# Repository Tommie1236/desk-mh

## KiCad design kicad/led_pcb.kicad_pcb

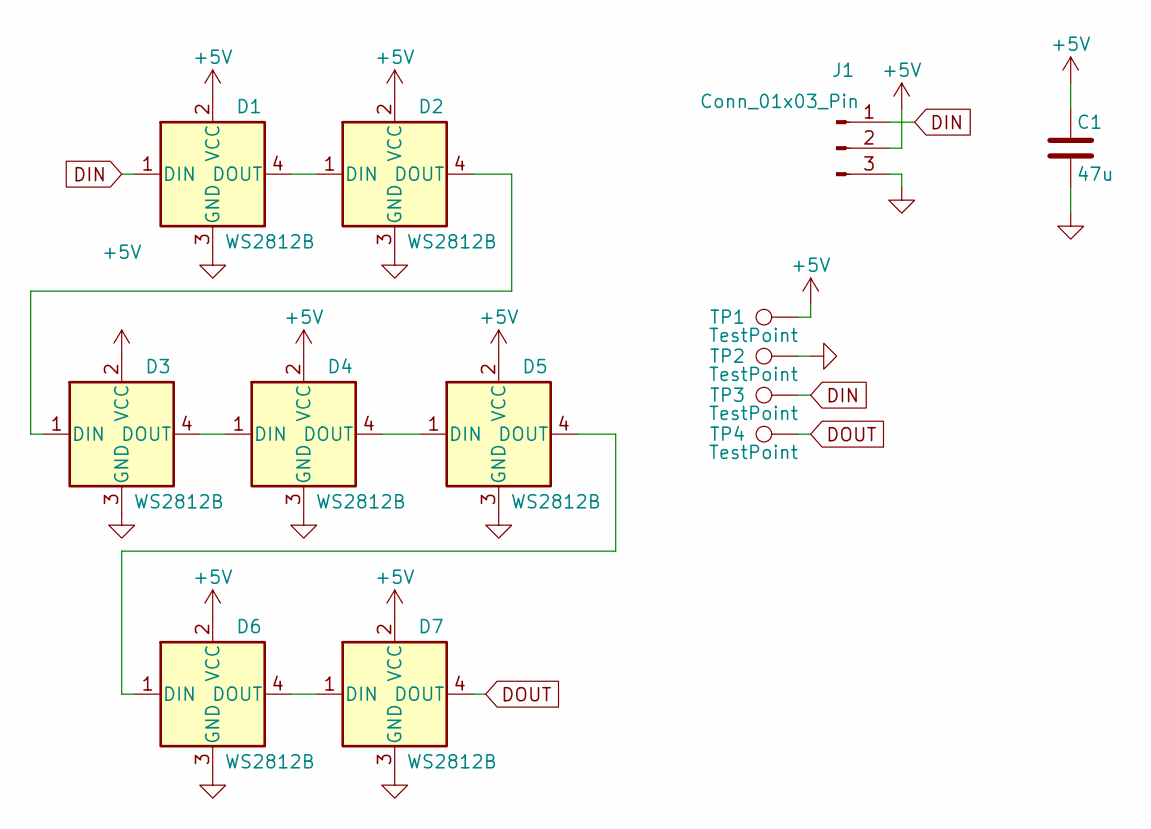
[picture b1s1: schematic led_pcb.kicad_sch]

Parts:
C1: 47u; C_1206_3216Metric
D1, D2, D3, D4, D5, D6, D7: WS2812B; 8mm 4pin
J1: Conn_01x03_Pin; PinHeader_1x03_P1.27mm_Vertical
TP1, TP2, TP3, TP4: TestPoint; TestPoint_Pad_D1.0mm

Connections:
+5V: C1.1, D1.2 (VCC), D2.2 (VCC), D3.2 (VCC), D4.2 (VCC), D5.2 (VCC), D6.2 (VCC), D7.2 (VCC), J1.2, TP1.1
DIN: D1.1 (DIN), J1.1, TP3.1
DOUT: D7.4 (DOUT), TP4.1
GND: C1.2, D1.3 (GND), D2.3 (GND), D3.3 (GND), D4.3 (GND), D5.3 (GND), D6.3 (GND), D7.3 (GND), J1.3, TP2.1
unnamed: D1.4 (DOUT), D2.1 (DIN)
unnamed: D2.4 (DOUT), D3.1 (DIN)
unnamed: D3.4 (DOUT), D4.1 (DIN)
unnamed: D4.4 (DOUT), D5.1 (DIN)
unnamed: D5.4 (DOUT), D6.1 (DIN)
unnamed: D6.4 (DOUT), D7.1 (DIN)

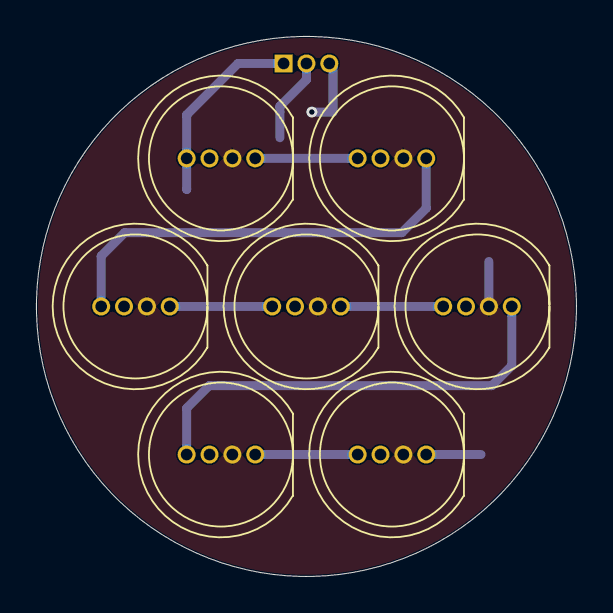
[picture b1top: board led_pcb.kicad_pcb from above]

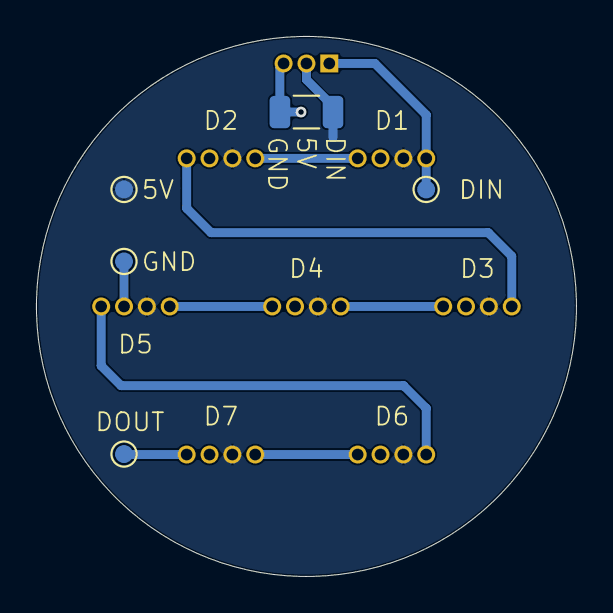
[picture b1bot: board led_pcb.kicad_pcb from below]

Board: 2 copper layers, 30.0 x 30.0 mm, 13 parts (6 on the bottom side), 10 nets.

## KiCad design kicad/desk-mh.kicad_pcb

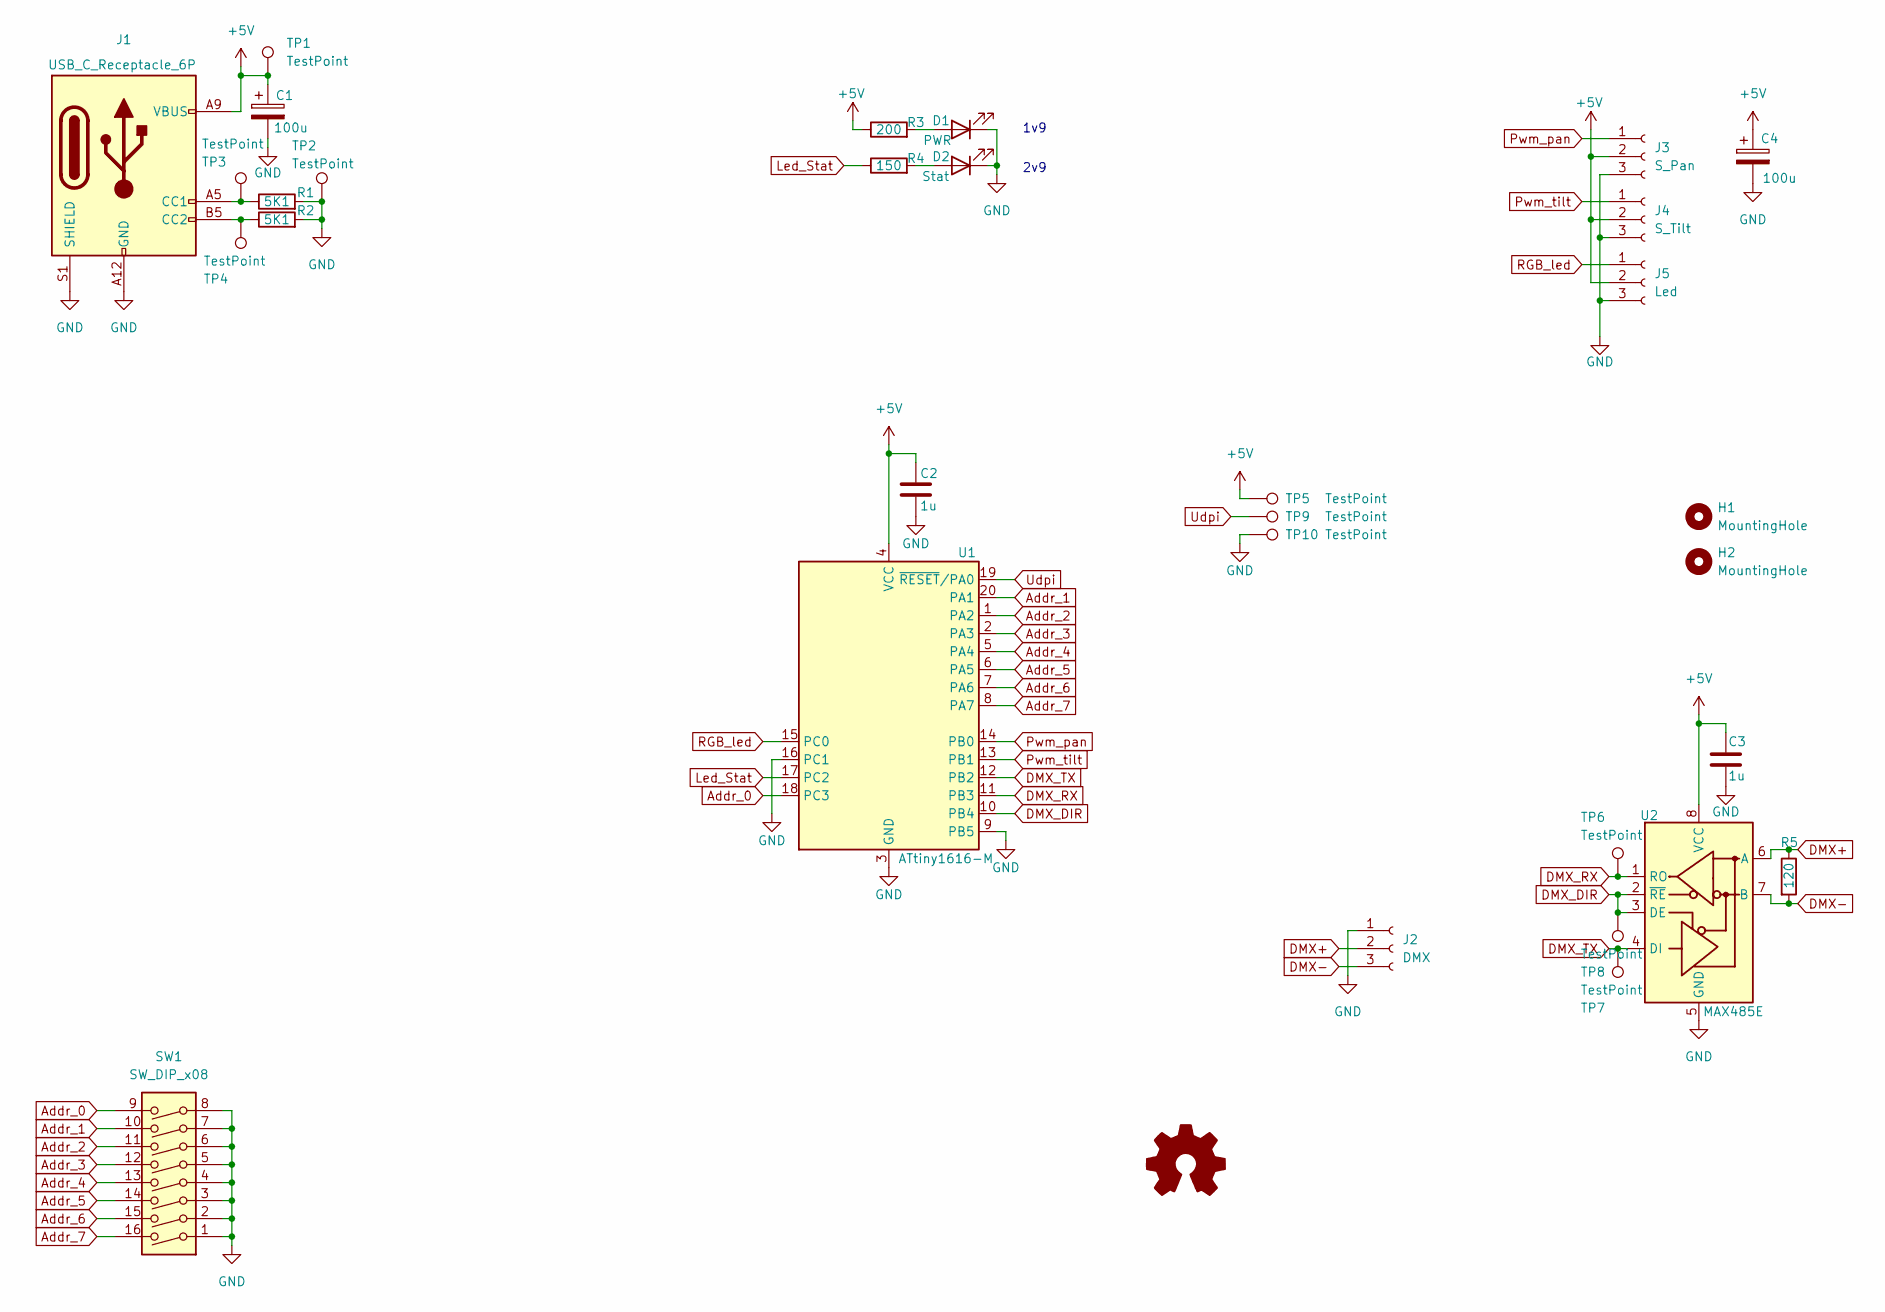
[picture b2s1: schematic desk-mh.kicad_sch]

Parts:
C1, C4: 100u; C_0805_2012Metric
C2, C3: 1u; C_0603_1608Metric
D1: PWR; LED_0805_2012Metric
D2: Stat; LED_0805_2012Metric
H1, H2: MountingHole; MountingHole_3.5mm
J1: USB_C_Receptacle_6P; USB_C_Receptacle_HRO_TYPE-C-31-M-17
J2: DMX; PinHeader_1x03_P1.27mm_Vertical
J3: S_Pan; PinHeader_1x03_P1.27mm_Vertical
J4: S_Tilt; PinHeader_1x03_P1.27mm_Vertical
J5: Led; PinHeader_1x03_P1.27mm_Vertical
R1, R2: 5K1; R_0603_1608Metric
R3: 200; R_0603_1608Metric
R4: 150; R_0603_1608Metric
R5: 120; R_0603_1608Metric
SW1: SW_DIP_x08; SOIC-16W_5.3x10.2mm_P1.27mm
SYM1: Logo_Open_Hardware_Small; OSHW-Logo2_7.3x6mm_SilkScreen
TP1, TP2, TP3, TP4, TP6, TP7, TP8: TestPoint; TestPoint_Pad_D1.0mm
TP5, TP9, TP10: TestPoint; TestPoint_Pad_D1.5mm
U1: ATtiny1616-M; VQFN-20-1EP_3x3mm_P0.4mm_EP1.7x1.7mm
U2: MAX485E; SOIC-8_3.9x4.9mm_P1.27mm

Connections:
+5V: C1.1, C2.1, C3.1, C4.1, J1.A9 (VBUS), J1.B9 (VBUS), J3.2, J4.2, J5.2, R3.1, TP1.1, TP5.1, U1.4 (VCC), U2.8 (VCC)
Addr_0: SW1.9, U1.18 (PC3)
Addr_1: SW1.10, U1.20 (PA1)
Addr_2: SW1.11, U1.1 (PA2)
Addr_3: SW1.12, U1.2 (PA3)
Addr_4: SW1.13, U1.5 (PA4)
Addr_5: SW1.14, U1.6 (PA5)
Addr_6: SW1.15, U1.7 (PA6)
Addr_7: SW1.16, U1.8 (PA7)
DMX+: J2.2, R5.1, U2.6 (A)
DMX-: J2.3, R5.2, U2.7 (B)
DMX_DIR: TP8.1, U1.10 (PB4), U2.2 (~RE), U2.3 (DE)
DMX_RX: TP6.1, U1.11 (PB3), U2.1 (RO)
DMX_TX: TP7.1, U1.12 (PB2), U2.4 (DI)
GND: C1.2, C2.2, C3.2, C4.2, D1.1 (K), D2.1 (K), J1.A12 (GND), J1.B12 (GND), J1.S1 (SHIELD), J2.1, J3.3, J4.3, J5.3, R1.2, R2.2, SW1.1, SW1.2, SW1.3, SW1.4, SW1.5, SW1.6, SW1.7, SW1.8, TP2.1, TP10.1, U1.3 (GND), U1.9 (PB5), U1.16 (PC1), U1.21 (GND), U2.5 (GND)
Led_Stat: R4.1, U1.17 (PC2)
unnamed: D1.2 (A), R3.2
unnamed: D2.2 (A), R4.2
unnamed: J1.A5 (CC1), R1.1, TP3.1
unnamed: J1.B5 (CC2), R2.1, TP4.1
Pwm_pan: J3.1, U1.14 (PB0)
Pwm_tilt: J4.1, U1.13 (PB1)
RGB_led: J5.1, U1.15 (PC0)
Udpi: TP9.1, U1.19 (~RESET/PA0)

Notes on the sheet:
2v9
1v9

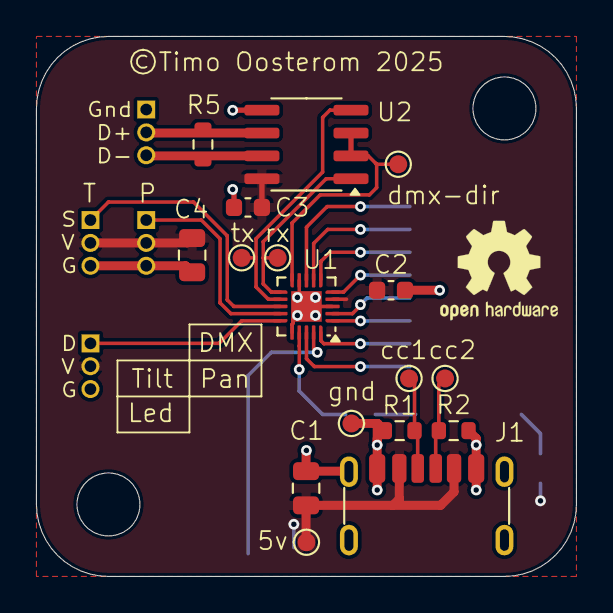
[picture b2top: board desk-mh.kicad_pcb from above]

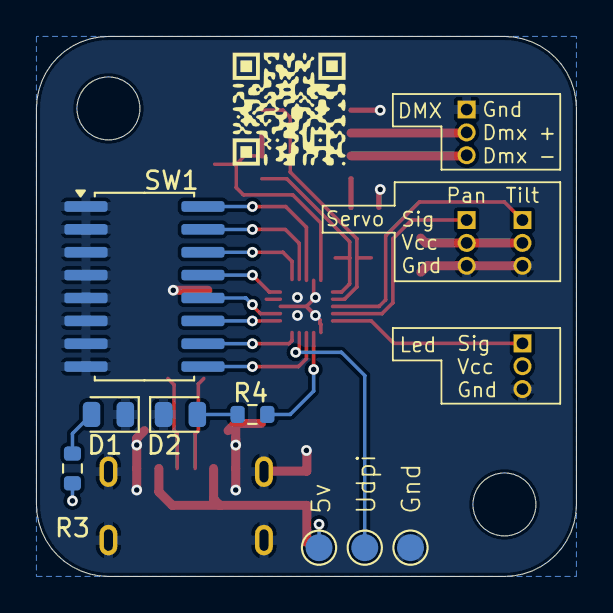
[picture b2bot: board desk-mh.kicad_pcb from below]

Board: 2 copper layers, 30.0 x 30.0 mm, 32 parts (8 on the bottom side), 24 nets.

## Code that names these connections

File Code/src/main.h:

#include <avr/io.h>


// dmx patch
// 1: pan
// 2: tilt
// 3: red1
// 4: green1
// 5: blue1
// 6-23: red/green/blue 2...7 (for mh wash)

#define PATCH_PAN_OFFSET        0
#define PATCH_TILT_OFFSET       1
#define PATCH_MASTER_OFFSET     2
#define PATCH_COLOR_OFFSET      3

//
//                x -------------- PA1 addr1
//                |  x ----------- PA0 updi/prog
//                |  |  x -------- PC3 addr0
//                |  |  |  x ----- PC2 Status led
//                |  |  |  |  x -- PC1 x
//               20 21 22 23 24
//    addr2 PA2 1               15 PC0 Led
//    addr3 PA3 2               14 PB0 Pan
//    gnd   gnd 3               13 PB1 Tilt
//    vcc   vcc 4               12 PB2 Dmx tx
//    addr4 PA4 5               11 PB3 Dmx rx
//                6  7  8  9 10 
//                |  |  |  |  x -- PB4 Dmx dir
//                |  |  |  x ----- PB5 x
//                |  |  x -------- PA7 addr7
//                |  x ----------- PA6 addr6
//                x -------------- PA5 addr5
//

// uncomment correct model
#define MH_SPOT
#define MH_WASH

#if (defined(MH_SPOT) == defined(MH_WASH))
    // TODO: uncomment error check
    //#error "Invalidd model configuration: choose either SPOT or WASH"
#endif

// TODO: defines still needed? using direct PORT/PIN numbers in code
// and the hardware is already made.
// Keeping it here for reference right now
#define ADDR0       22
#define ADDR1       20
#define ADDR2       1
#define ADDR3       2
#define ADDR4       5
#define ADDR5       6
#define ADDR6       7
#define ADDR7       8

#define DMX_DIR     10
#define DMX_RX      11
#define DMX_TX      12

#define PWM_TILT    13
#define PWM_PAN     14
#define LED         15

#define STATUS_LED  23

// g r b ??
typedef struct {
    uint8_t red;
    uint8_t green;
    uint8_t blue;
} color_t;

typedef struct {
    uint8_t position_updated;
    uint8_t led_updated;
} status_t;

void setup_io();

uint8_t read_address();

void set_servos(uint8_t pan, uint8_t tilt);

void set_led_color(color_t *color);

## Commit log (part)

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2025-10-16 uploaded files
2025-10-16 started 3d model
2025-10-17 moved to make instead of platformio and cleaned up repo
2025-10-17 added freecad backups to gitignore
2025-10-17 finished bottom cover and pcb part of base
2025-10-17 added servo and pcb models
2025-10-18 progress
2025-10-25 created test program (the hardware works) but am still stuck on 3.33Mhz instead of 20Mhz. sadly
2025-10-25 updated makefile to program via a usb-uart instead of jtag2updi.
2026-04-29 worked on some code. cleanup and progress
2026-04-29 added led pcb to repo and cleaned up kicad folder
2026-04-30 don't know what changed, little ago and git doesn't support binary diffs

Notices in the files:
kicad/desk-mh.kicad_pcb:
©Timo Oosterom 2025
